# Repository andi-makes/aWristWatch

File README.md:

# andi makes a wrist watch! ⌚
> *It ain't pretty, but it's **mine**!* 😄

## Hardware 💡
### Microcontroller
The microcontroller used by this project is the `STM32L011F4` from STM. 
It features many peripherals as well as low power operation features.

### Display
This watch displays the time using four `KCSA02-105` 7-Segment displays from 
Kingbright. They were chosen because of their small footprint. Those 7-Segment 
displays are driven by the `STP08DP05` serial constant current driver from STM.

### Power
In it's normal operation, the watch gets powered by a LIPO battery. It can also 
be powered by an external powersource which provides 5V. The external connection
is also used to charge the internal LIPO using a `MCP73831` charger IC from 
Microchip. For OR-ing those two power supplies together so that the battery
is not used for powering the circuit during charging two `LM66100` ideal diodes
are used. The resulting powerline gets regulated by a `TLV70033` linear voltage 
regulator. The resulting 3.3V are used to power the microcontroller. For the 
powersupply for the display the non regulated voltage is used.

## Firmware 🧠

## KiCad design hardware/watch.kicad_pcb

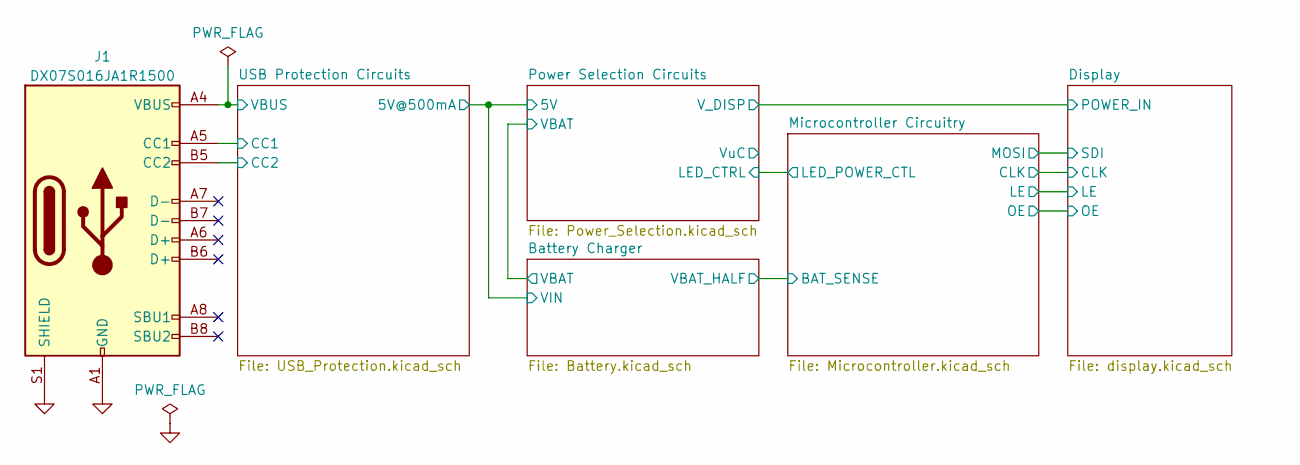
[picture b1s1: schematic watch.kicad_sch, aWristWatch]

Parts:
J1: DX07S016JA1R1500

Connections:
/USB Protection Circuits/CC1: J1.A5 (CC1); also elsewhere on the board
/USB Protection Circuits/CC2: J1.B5 (CC2); also elsewhere on the board
/USB Protection Circuits/VBUS: J1.A4 (VBUS), J1.A9 (VBUS), J1.B4 (VBUS), J1.B9 (VBUS); also elsewhere on the board
GND: J1.A1 (GND), J1.A12 (GND), J1.B1 (GND), J1.B12 (GND), J1.S1 (SHIELD); also elsewhere on the board

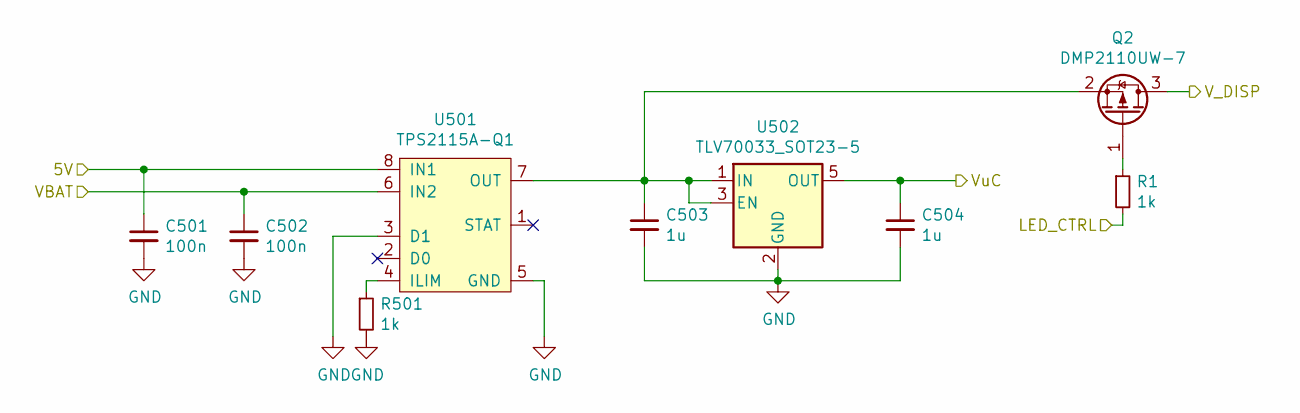
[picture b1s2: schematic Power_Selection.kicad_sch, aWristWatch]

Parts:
C501, C502: 100n; C_0603_1608Metric
C503, C504: 1u; C_0603_1608Metric
Q2: DMP2110UW-7; SOT-323_SC-70
R1, R501: 1k; R_0603_1608Metric
U501: TPS2115A-Q1; TSSOP-8_3x6.4_P0.65mm
U502: TLV70033_SOT23-5; SOT-23-5

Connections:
/Battery Charger/VBAT: C502.1, U501.6 (IN2); also elsewhere on the board
/Display/POWER_IN: Q2.3 (D); also elsewhere on the board
/Power Selection Circuits/5V: C501.1, U501.8 (IN1); also elsewhere on the board
/Power Selection Circuits/LED_CTRL: R1.2; also elsewhere on the board
/Power Selection Circuits/VuC: C504.1, U502.5 (OUT)
GND: C501.2, C502.2, C503.2, C504.2, R501.2, U501.3 (D1), U501.5 (GND), U502.2 (GND); also elsewhere on the board
unnamed: C503.1, Q2.2 (S), U501.7 (OUT), U502.1 (IN), U502.3 (EN)
unnamed: Q2.1 (G), R1.1
unnamed: R501.1, U501.4 (ILIM)

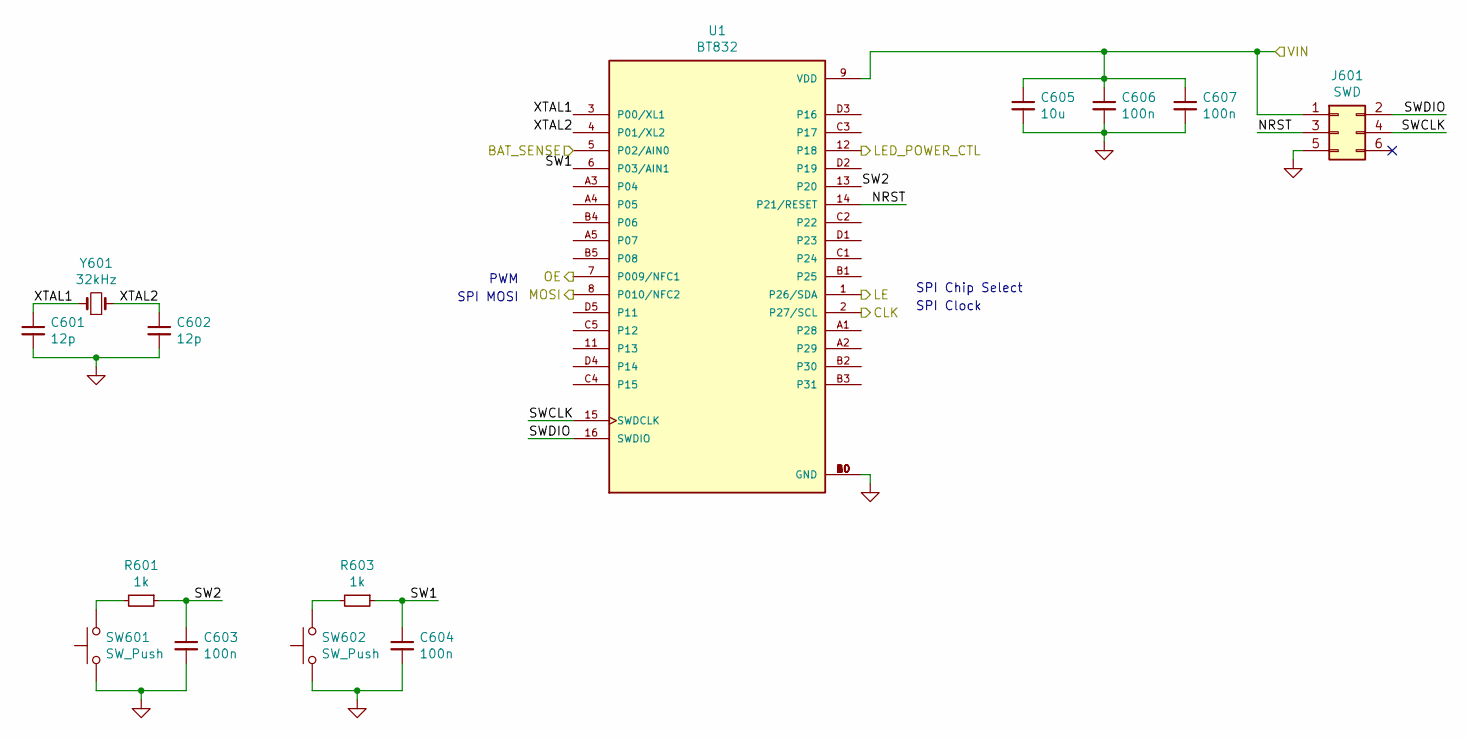
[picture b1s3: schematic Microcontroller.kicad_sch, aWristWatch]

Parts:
C601, C602: 12p; C_0603_1608Metric
C603, C604, C606, C607: 100n; C_0603_1608Metric
C605: 10u; C_0805_2012Metric
J601: SWD; Tag-Connect_TC2030-IDC-NL_2x03_P1.27mm_Vertical
R601, R603: 1k; R_0603_1608Metric
SW601, SW602: SW_Push; SW_Push_1P1T_NO_CK_KMR2
U1: BT832; BLEMODULE_BT832; PARTREV 2.04
Y601: 32kHz; Crystal_SMD_3215-2Pin_3.2x1.5mm

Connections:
/Display/CLK: U1.2 (P27/SCL); also elsewhere on the board
/Display/LE: U1.1 (P26/SDA); also elsewhere on the board
/Display/OE: U1.7 (P009/NFC1); also elsewhere on the board
/Microcontroller Circuitry/BAT_SENSE: U1.5 (P02/AIN0); also elsewhere on the board
/Microcontroller Circuitry/MOSI: U1.8 (P010/NFC2); also elsewhere on the board
/Microcontroller Circuitry/NRST: J601.3, U1.14 (P21/RESET)
/Microcontroller Circuitry/SW1: C604.1, R603.1, U1.6 (P03/AIN1)
/Microcontroller Circuitry/SW2: C603.1, R601.1, U1.13 (P20)
/Microcontroller Circuitry/SWCLK: J601.4, U1.15 (SWDCLK)
/Microcontroller Circuitry/SWDIO: J601.2, U1.16 (SWDIO)
/Microcontroller Circuitry/VIN: C605.1, C606.1, C607.1, J601.1, U1.9 (VDD)
/Microcontroller Circuitry/XTAL1: C601.1, U1.3 (P00/XL1), Y601.1
/Microcontroller Circuitry/XTAL2: C602.1, U1.4 (P01/XL2), Y601.2
/Power Selection Circuits/LED_CTRL: U1.12 (P18); also elsewhere on the board
GND: C601.2, C602.2, C603.2, C604.2, C605.2, C606.2, C607.2, J601.5, SW601.1, SW602.1, U1.10 (GND), U1.A0 (GND), U1.B0 (GND), U1.C0 (GND), U1.D0 (GND); also elsewhere on the board
unnamed: R601.2, SW601.2
unnamed: R603.2, SW602.2

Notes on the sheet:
SPI MOSI
SPI Chip Select
PWM
SPI Clock

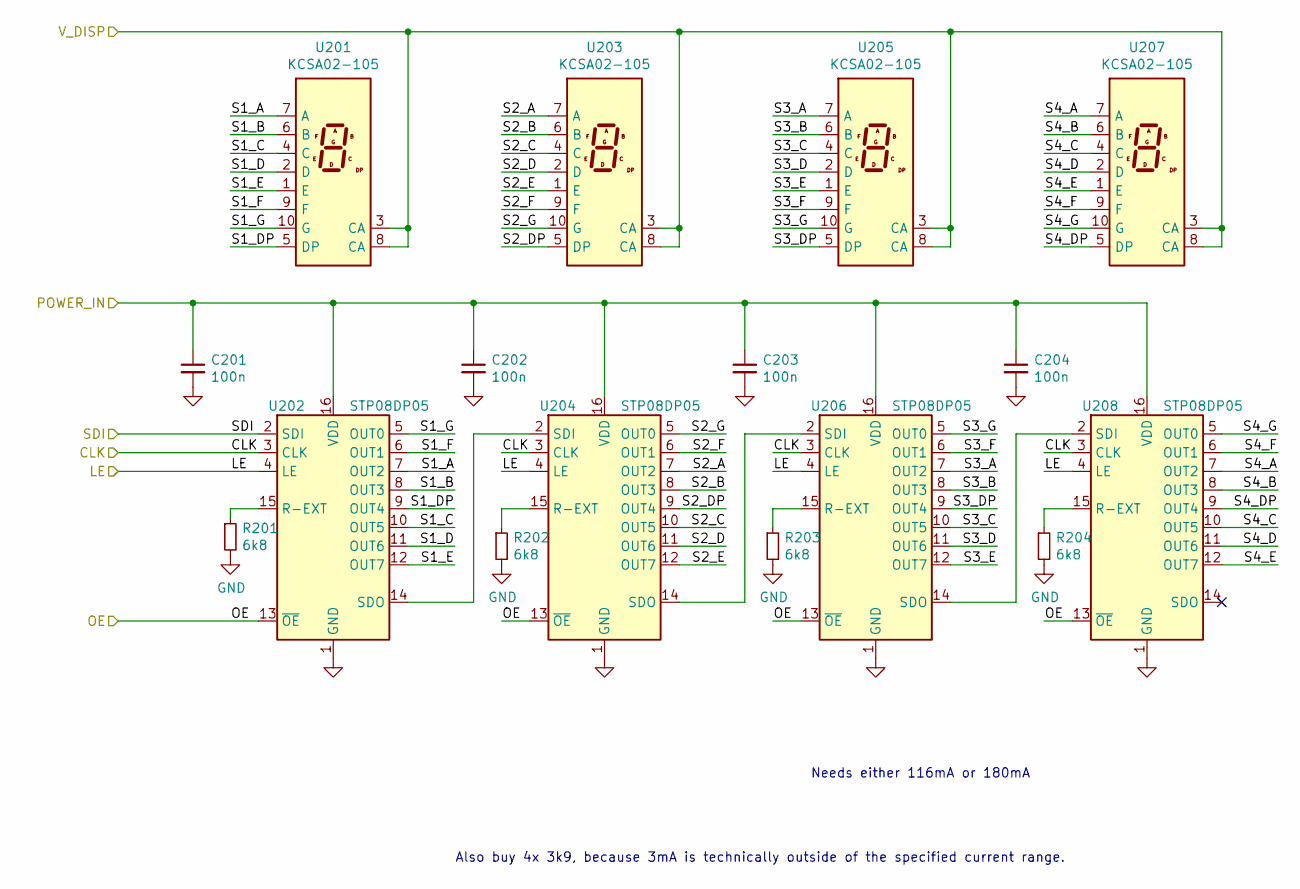
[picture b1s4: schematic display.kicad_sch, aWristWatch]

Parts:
C201, C202, C203, C204: 100n; C_0603_1608Metric
R201, R202, R203, R204: 6k8; R_0603_1608Metric
U201, U203, U205, U207: KCSA02-105; KCSC02-105
U202, U204, U206, U208: STP08DP05; TSSOP-16_4.4x5mm_P0.65mm; Part Number STP08DP05TTR

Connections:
/Display/CLK: U202.3 (CLK), U204.3 (CLK), U206.3 (CLK), U208.3 (CLK); also elsewhere on the board
/Display/LE: U202.4 (LE), U204.4 (LE), U206.4 (LE), U208.4 (LE); also elsewhere on the board
/Display/OE: U202.13 (~OE), U204.13 (~OE), U206.13 (~OE), U208.13 (~OE); also elsewhere on the board
/Display/POWER_IN: C201.1, C202.1, C203.1, C204.1, U202.16 (VDD), U204.16 (VDD), U206.16 (VDD), U208.16 (VDD); also elsewhere on the board
/Display/S1_A: U201.7 (A), U202.7 (OUT2)
/Display/S1_B: U201.6 (B), U202.8 (OUT3)
/Display/S1_C: U201.4 (C), U202.10 (OUT5)
/Display/S1_D: U201.2 (D), U202.11 (OUT6)
/Display/S1_DP: U201.5 (DP), U202.9 (OUT4)
/Display/S1_E: U201.1 (E), U202.12 (OUT7)
/Display/S1_F: U201.9 (F), U202.6 (OUT1)
/Display/S1_G: U201.10 (G), U202.5 (OUT0)
/Display/S2_A: U203.7 (A), U204.7 (OUT2)
/Display/S2_B: U203.6 (B), U204.8 (OUT3)
/Display/S2_C: U203.4 (C), U204.10 (OUT5)
/Display/S2_D: U203.2 (D), U204.11 (OUT6)
/Display/S2_DP: U203.5 (DP), U204.9 (OUT4)
/Display/S2_E: U203.1 (E), U204.12 (OUT7)
/Display/S2_F: U203.9 (F), U204.6 (OUT1)
/Display/S2_G: U203.10 (G), U204.5 (OUT0)
/Display/S3_A: U205.7 (A), U206.7 (OUT2)
/Display/S3_B: U205.6 (B), U206.8 (OUT3)
/Display/S3_C: U205.4 (C), U206.10 (OUT5)
/Display/S3_D: U205.2 (D), U206.11 (OUT6)
/Display/S3_DP: U205.5 (DP), U206.9 (OUT4)
/Display/S3_E: U205.1 (E), U206.12 (OUT7)
/Display/S3_F: U205.9 (F), U206.6 (OUT1)
/Display/S3_G: U205.10 (G), U206.5 (OUT0)
/Display/S4_A: U207.7 (A), U208.7 (OUT2)
/Display/S4_B: U207.6 (B), U208.8 (OUT3)
/Display/S4_C: U207.4 (C), U208.10 (OUT5)
/Display/S4_D: U207.2 (D), U208.11 (OUT6)
/Display/S4_DP: U207.5 (DP), U208.9 (OUT4)
/Display/S4_E: U207.1 (E), U208.12 (OUT7)
/Display/S4_F: U207.9 (F), U208.6 (OUT1)
/Display/S4_G: U207.10 (G), U208.5 (OUT0)
/Display/V_DISP: U201.3 (CA), U201.8 (CA), U203.3 (CA), U203.8 (CA), U205.3 (CA), U205.8 (CA), U207.3 (CA), U207.8 (CA)
/Microcontroller Circuitry/MOSI: U202.2 (SDI); also elsewhere on the board
GND: C201.2, C202.2, C203.2, C204.2, R201.2, R202.2, R203.2, R204.2, U202.1 (GND), U204.1 (GND), U206.1 (GND), U208.1 (GND); also elsewhere on the board
unnamed: R201.1, U202.15 (R-EXT)
unnamed: R202.1, U204.15 (R-EXT)
unnamed: R203.1, U206.15 (R-EXT)
unnamed: R204.1, U208.15 (R-EXT)
unnamed: U202.14 (SDO), U204.2 (SDI)
unnamed: U204.14 (SDO), U206.2 (SDI)
unnamed: U206.14 (SDO), U208.2 (SDI)

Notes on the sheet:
Needs either 116mA or 180mA
Also buy 4x 3k9, because 3mA is technically outside of the specified current range.

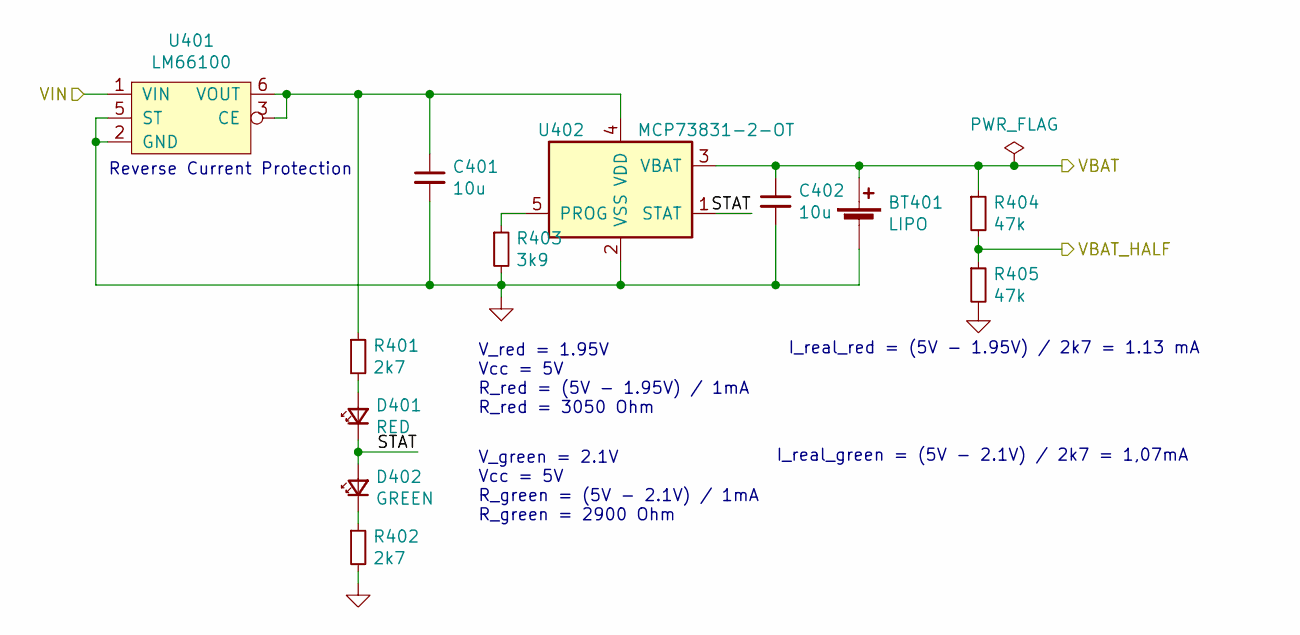
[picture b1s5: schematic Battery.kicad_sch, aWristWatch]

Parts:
BT401: LIPO; PinHeader_1x02_P2.54mm_Vertical
C401, C402: 10u; C_0805_2012Metric
D401: RED; LED_0603_1608Metric; Part Number AA1608SURSK
D402: GREEN; LED_0603_1608Metric; Part Number AA1608CGSK
R401, R402: 2k7; R_0603_1608Metric
R403: 3k9; R_0603_1608Metric
R404, R405: 47k; R_0603_1608Metric
U401: LM66100; Sc70-6
U402: MCP73831-2-OT; SOT-23-5

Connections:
/Battery Charger/STAT: D401.1 (K), D402.2 (A), U402.1 (STAT)
/Battery Charger/VBAT: BT401.1 (+), C402.1, R404.1, U402.3 (VBAT); also elsewhere on the board
/Microcontroller Circuitry/BAT_SENSE: R404.2, R405.1; also elsewhere on the board
/Power Selection Circuits/5V: U401.1 (VIN); also elsewhere on the board
GND: BT401.2 (-), C401.2, C402.2, R402.2, R403.2, R405.2, U401.2 (GND), U401.5 (ST), U402.2 (VSS); also elsewhere on the board
unnamed: C401.1, R401.1, U401.3 (CE), U401.6 (VOUT), U402.4 (VDD)
unnamed: D401.2 (A), R401.2
unnamed: D402.1 (K), R402.1
unnamed: R403.1, U402.5 (PROG)

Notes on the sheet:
V_red = 1.95V Vcc = 5V R_red = (5V - 1.95V) / 1mA R_red = 3050 Ohm
Reverse Current Protection
V_green = 2.1V Vcc = 5V R_green = (5V - 2.1V) / 1mA R_green = 2900 Ohm
I_real_red = (5V - 1.95V) / 2k7 = 1.13 mA
I_real_green = (5V - 2.1V) / 2k7 = 1,07mA

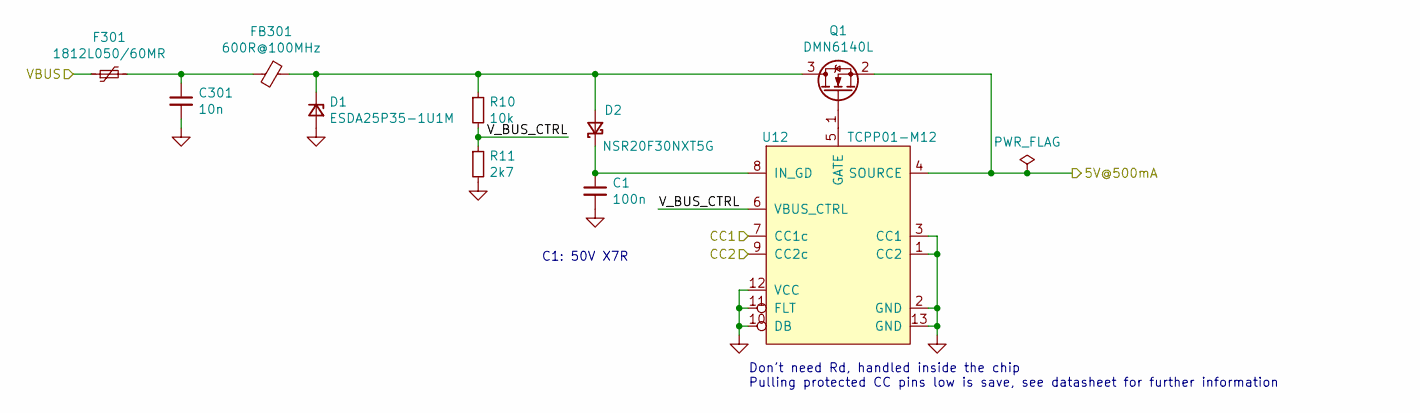
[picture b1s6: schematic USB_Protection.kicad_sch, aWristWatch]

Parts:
C1: 100n; C_0603_1608Metric
C301: 10n; C_0603_1608Metric
D1: ESDA25P35-1U1M; D_0603_1608Metric
D2: NSR20F30NXT5G; D_0603_1608Metric
F301: 1812L050/60MR; Fuse_1812_4532Metric
FB301: 600R@100MHz; L_0603_1608Metric
Q1: DMN6140L; SOT-23
R10: 10k; R_0603_1608Metric
R11: 2k7; R_0603_1608Metric
U12: TCPP01-M12; QFN-12-1EP_3x3mm_P0.51mm_EP1.45x1.45mm

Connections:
/Power Selection Circuits/5V: Q1.2 (S), U12.4 (SOURCE); also elsewhere on the board
/USB Protection Circuits/CC1: U12.7 (CC1c); also elsewhere on the board
/USB Protection Circuits/CC2: U12.9 (CC2c); also elsewhere on the board
/USB Protection Circuits/VBUS: F301.1; also elsewhere on the board
/USB Protection Circuits/V_BUS_CTRL: R10.2, R11.1, U12.6 (VBUS_CTRL)
GND: C1.2, C301.2, D1.2 (A), R11.2, U12.1 (CC2), U12.2 (GND), U12.3 (CC1), U12.10 (DB), U12.11 (FLT), U12.12 (VCC), U12.13 (GND); also elsewhere on the board
unnamed: C1.1, D2.1 (K), U12.8 (IN_GD)
unnamed: C301.1, F301.2, FB301.2
unnamed: D1.1 (K), D2.2 (A), FB301.1, Q1.3 (D), R10.1
unnamed: Q1.1 (G), U12.5 (GATE)

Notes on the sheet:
C1: 50V X7R
Don't need Rd, handled inside the chip Pulling protected CC pins low is save, see datasheet for further information

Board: 4 copper layers, 62 parts (22 on the bottom side), 77 nets, no tracks yet.

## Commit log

2020-09-26 added pcb to git
2020-12-16 hardware revision
2020-12-16 firmware initial commit
2020-12-16 added utility functions to gpio.h
2020-12-17 finished code for gpio.h
2020-12-17 Added some register descriptions to lptim.h
2020-12-19 updated gpio and pin
2020-12-20 abstraction layer for lptim
2020-12-21 refactored pwr
2020-12-21 began refactoring of rtc
2020-12-26 refactored display.h/.cpp
2020-12-27 introduced bits.h and fields.h
2020-12-30 Fixed compiler warning
2020-12-30 began implementing concepts
2021-01-03 introduced interrupts.h
2021-01-03 cleaned up cmake files
2021-01-03 added gpio::enable
2021-01-04 refactored
2021-01-04 updated lptim
2021-01-04 more consistent use of zol::addr_t
2021-01-05 fixed bits.h and fields.h
2021-01-05 used bits and fields in rtc header
2021-01-05 added bitrs
2021-01-05 made field -> field_rw and introduced field_r
2021-01-05 fixed stuff
2021-01-05 Added bits and fields to rcc.h
2021-01-05 used new functionality provided by rcc.h
2021-01-06 I am able to set my watch :D
2021-01-06 it can display time, date and the year now!
2021-01-10 added adc.h
2021-01-10 refactored rtc.h
2021-01-10 forgot to implement adc::enable
2021-01-15 initial battery indicator support
2021-01-17 fixed bug in bits.h
2021-01-17 made display constructor unaccessible
2021-01-17 introduced dma.h
2021-01-17 added some functionality to adc.h
2021-01-17 added battery.h Battery level menu now uses DMA :D
2021-01-17 update display driver
2021-01-24 disp/edit brightness and standby auto off
2021-02-01 case design
2021-02-05 updated firmware
2021-02-05 case design files
2021-02-14 updated case design
2021-02-14 included up-to-date hardware revision
2021-02-16 optimised reg::set_bit function
2021-02-16 Describe Hardware in README.md
2021-02-16 new case iteration
2021-02-16 cleanup of files in model folder
2021-02-16 refactored register.h
2021-02-18 added vscode tasks.json file
2021-02-18 removed display point data and vrefint from main
2021-02-18 removed some states from state machine
2021-02-18 Added more warnings to build
    Added the Warning Flags `-Wextra`, `-pedantic` and fixed all warnings
2021-02-21 rewrote adc algorithm
2021-02-21 wakeup input bug fixed
2021-02-22 renamed .h files to hpp and cmake stuff
2021-02-26 dockerfile
2021-02-27 fixed errors from removing submodule
2021-02-27 docker wip
    Added the propably simplest devcontainer vscode file
    Adapted Dockerfile to ubuntu:20.04
    cleaned up chip/stm32l011.cmake
    removed clangtidy and iwyu functionality from the cmake file
    Compiling in the container works.
2021-02-27 Ignored bom file
2021-02-28 Made Docker image slightly smaller
2021-02-28 Added a README
2021-02-28 removed lib folder
2021-02-28 added build docker target
2021-02-28 Better build (#2)
    * renamed .h files to hpp and cmake stuff
    * dockerfile
    * fixed errors from removing submodule
    * docker wip
    Added the propably simplest devcontainer vscode file
    Adapted Dockerfile to ubuntu:20.04
2021-02-28 #1.3
2021-02-28 refactoring based on issue #1 point 2
2021-03-01 More refactoring based on #1.2
2021-03-01 refactoring based on #1.1
2021-03-01 marked constructors of static only struct `delete`
2021-03-01 refactoring
2021-03-01 moved rtc_irqhandler into time.cpp
    Fixes #1
2021-03-01 Issue 1 (#3)
    * #1.3
    * refactoring based on issue #1 point 2
    * More refactoring based on #1.2
    * refactoring based on #1.1
    * marked constructors of static only struct `delete`
    * refactoring
2021-03-01 changed indentation to spaces
    after all this time, I am certain that spaces are superior.
    Don't fight me
2021-03-01 WIP Adding static analyzers
    cppcheck is working, but clang-tidy is... special.
    Can't really use the cmake functions for integrating those tools,
    because I want to store the output of the tools in files. The problem is
    that cmake invokes the tools on an file per file basis, which means that
    the output files would get overridden by the next compiled file.
    cppcheck is intelligent enough to get the needed input files out of the
2021-03-02 fixed clang-tidy problem
    Fixed it by writing a little python script,
    which parses the compile_commands.json file.
    It directly runs clang-tidy from the script with all source files.
2021-03-02 added more vscode tasks
2021-03-02 fix clang-tidy.py lockup
2021-03-02 added reconfigure clean script
2021-03-02 use target_compile_XXX instead add_compile_options
2021-03-02 added analyze target The analyze target will run all enabled analyzers.
2021-03-02 fixed cppcheck warnings
2021-03-02 fixed all gcc warnings
2021-03-04 Fixed all clang-tidy warnings except magic numbers
2021-03-04 updated clang-tidy.py
    Feature: Get the amount of warnings out of the clang-tidy.yml file
2021-03-05 renamed `enable` functions to power_on introduced intrrupt::enable/disable
2021-03-24 working on hardware rev3
2021-03-25 fixed usb type c cc pin termination
2021-03-25 reverse current protection
2021-03-25 hardware development
2021-03-26 schematic should be done, pcb is next
2021-03-31 wip hw
2021-04-01 finished routing
2021-04-01 calc current consumption
2021-04-01 calculate current consumption
2021-04-02 added 3d models
2021-04-02 file cleanup
2021-04-03 added some vias to gnd plane
2021-04-04 added powerflags
2021-04-04 minor improvements
2021-04-05 updated schematic info
2021-04-05 more stitching vias
2021-04-05 added order references to parts
2021-04-06 modified bom
2021-04-07 Fixed outdated BOM Item
2021-04-24 Fixed two hardware issues.
    Issue 1: Swapped USB D+/- lines
    Issue 2: Wrong schematic smybol for power switch
2021-04-30 new case
2021-05-04 added svd file to repo
2021-05-04 fixed critical bug within reg::or_together
2021-05-04 fixed bug in bit_rs::set
2021-05-04 adapted display driver for hw3
2021-05-04 fixed rtc isr bug
2021-05-04 smaller button
2021-05-04 bigger case
2021-05-05 [fw] fixed rtc init bug
2021-05-05 [fw] fixed battery level bug
2021-05-06 Hw3 (#4)
    * working on hardware rev3
    * fixed usb type c cc pin termination
    * reverse current protection
    * hardware development
    * schematic should be done, pcb is next
    * wip hw
2021-05-08 fixed input bug
2021-05-08 Fixed date glitch
2021-05-08 fixed time display bug
2021-05-08 fixed diplay off bug
2021-05-08 fixed display glitching at higher brightness
2021-05-08 increased refresh rate AND DAAAM, that's SMOOTH!
2021-05-17 modified case and wip endcap for wrist-band
2021-05-17 modified clang-tidy - Fixed unknown-warning-option - Fixed some clang-tidy warning - removed magic numbers from clang-tidy for now
2021-09-01 implemented stop sleep mode
    And I know, this is an unverified commit,
    I need to set up my gpg key on the new
    system
2021-09-05 clang-format
2021-10-30 [firmware] refactor code
2021-11-12 New uC, ditched FTDI chip, and more!
    Need to improve the schematic a little bit more.
    For example, I want to be able to turn the LED Drivers off using
    a MOSFET.
    For the PCB Layout: I want to move as many components as possible
    to the top layer, so that they are visible when in the case.
    Also, I have to consider solderability of the components, the more
2021-12-31 Updated to KiCad v6.0
